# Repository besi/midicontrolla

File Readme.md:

# MidiControlla
Custom Midi controller

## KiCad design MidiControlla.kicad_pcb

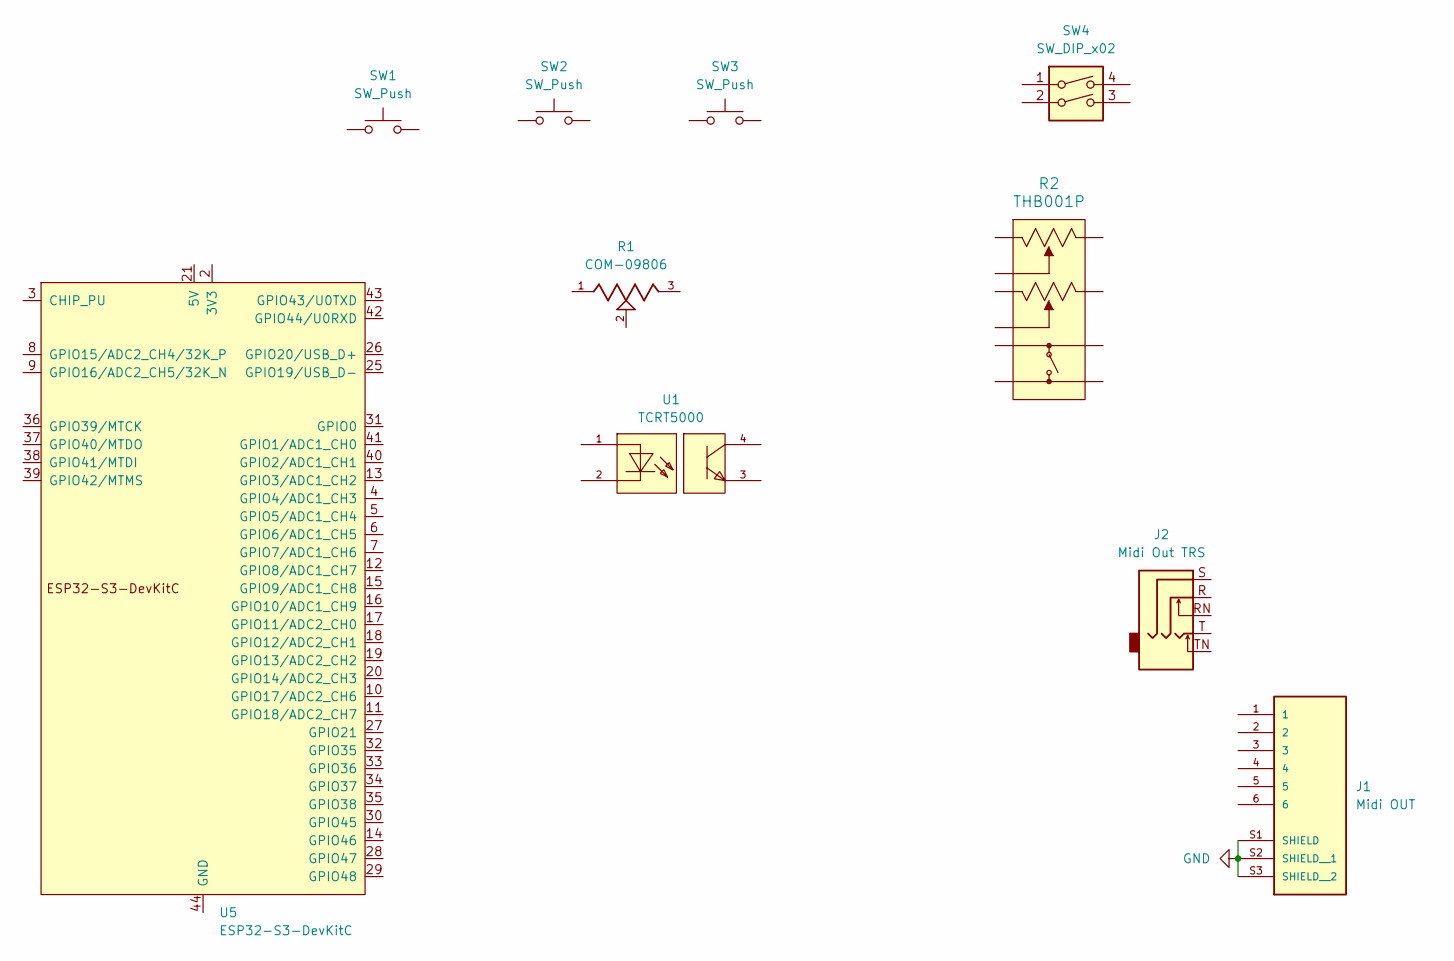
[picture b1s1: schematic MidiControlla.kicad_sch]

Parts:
J1: Midi OUT; MD-60SM; PARTREV 02/18/2022
J2: Midi Out TRS; Jack_3.5mm_CUI_SJ2-3593D-SMT_Horizontal
R1: COM-09806
R2: THB001P
SW1, SW2, SW3: SW_Push; pts636
SW4: SW_DIP_x02; SW_DIP_SPSTx02_Slide_6.7x6.64mm_W7.62mm_P2.54mm_LowProfile
U1: TCRT5000; OPTO-TH_TCRT5000; LCSC C2984661
U5: ESP32-S3-DevKitC

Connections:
GND: J1.S1 (SHIELD), J1.S2 (SHIELD__1), J1.S3 (SHIELD__2)
unnamed: U5.1 (3V3), U5.2 (3V3)
unnamed: U5.22 (GND), U5.23 (GND), U5.24 (GND), U5.44 (GND)

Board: 2 copper layers, 13 parts (0 on the bottom side), 3 nets, no tracks yet.

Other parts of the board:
R1#2, R1#3, R1#4: COM-09806

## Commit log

2024-07-11 Add software example based on circuit python and the adafruit_midi library
2024-07-11 Add basic kicad project with TCRT5000 IR distance sensor
2025-02-02 Add espressif c3
2025-03-31 Add footprints
